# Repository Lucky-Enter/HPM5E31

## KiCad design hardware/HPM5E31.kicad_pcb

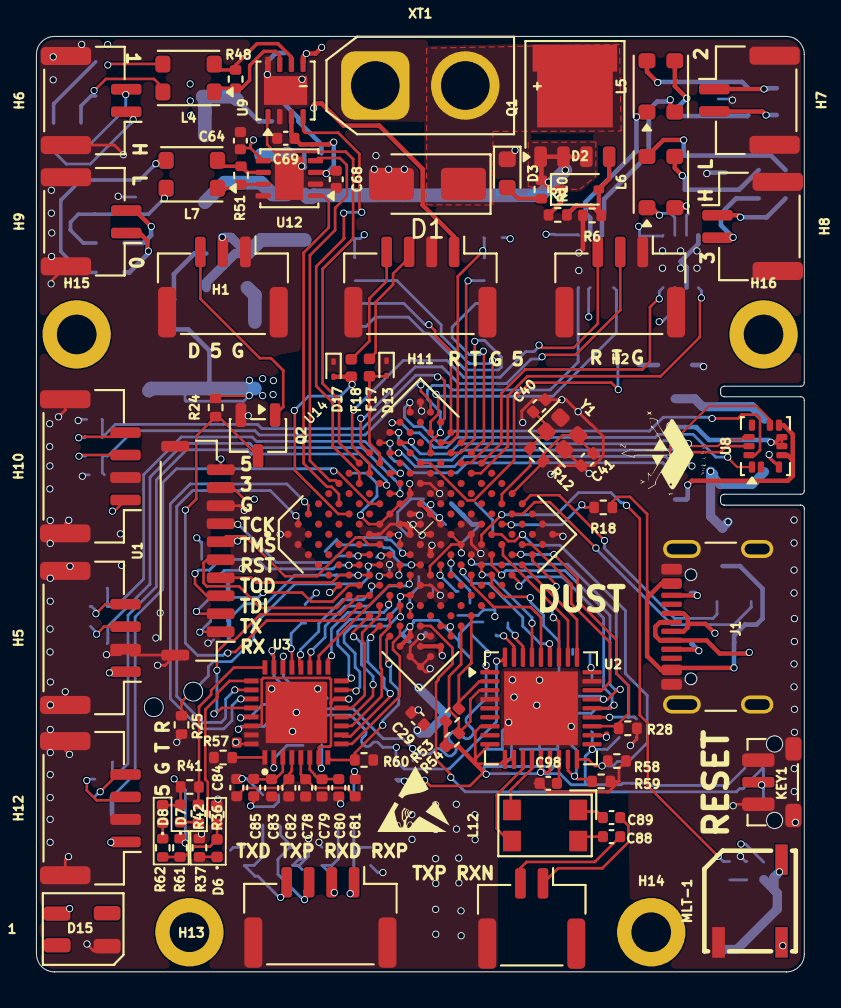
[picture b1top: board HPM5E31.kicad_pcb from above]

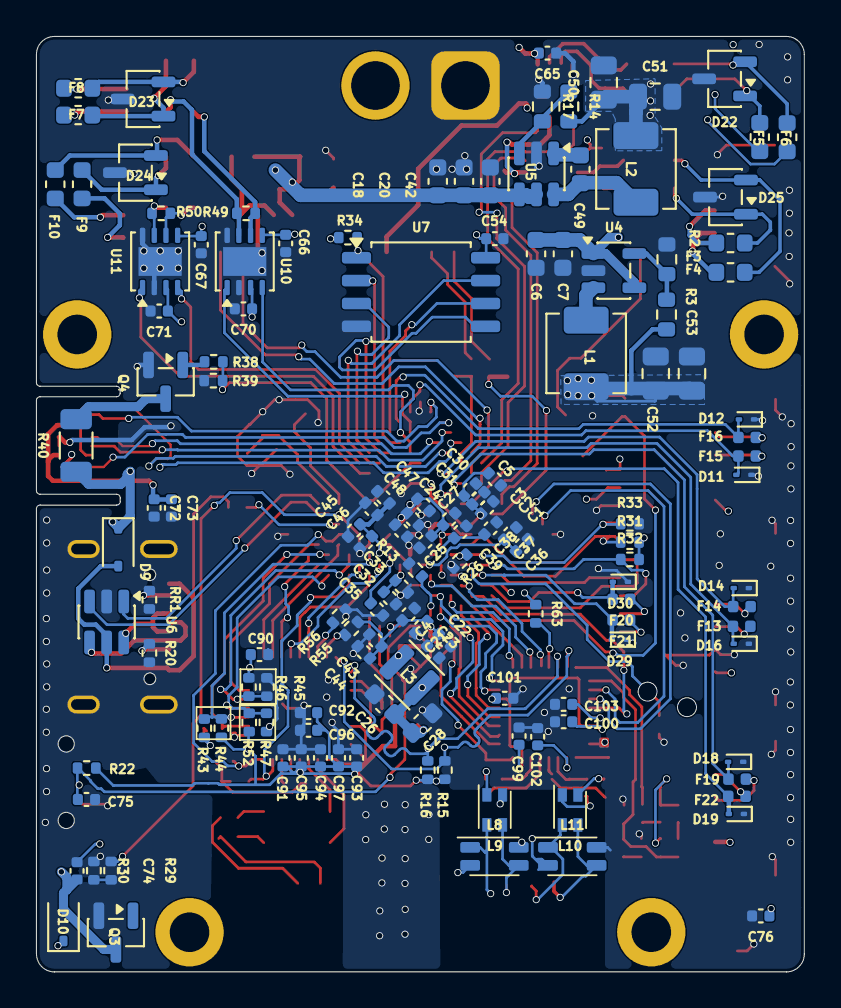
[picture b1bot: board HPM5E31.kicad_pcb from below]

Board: 4 copper layers, 42.7 x 52.0 mm, 223 parts (138 on the bottom side), 174 nets.

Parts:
C1, C2, C3, C4, C5, C22, C23, C24, C25, C27, C29, C30, C31, C32, C36, C38, C43, C46, C48, C54, C64, C65, C66, C67, C68, C69, C70, C71, C72, C73, C74, C75, C76, C80, C81, C84, C85, C88, C89, C90, C91, C92, C93, C94, C95, C96, C97, C99, C100, C101, C102, C103: 100nF; C_0402_1005Metric
C6, C7, C18, C20, C42: 10uF; C_0603_1608Metric
C21, C37, C39: 10uF; C_0402_1005Metric
C26, C28: 22uF; C_0603_1608Metric
C33, C35, C44, C45, C47: 4.7uF; C_0402_1005Metric
C40, C41: 12pF; C_0402_1005Metric
C49: 100nF; C_0603_1608Metric
C50, C51, C52, C53: 22uF 10V; C_0805_2012Metric
C78, C79, C82, C83: 10pF; C_0402_1005Metric
C98: 470nF; C_0402_1005Metric
D1: SMBJ30A; D_SMA
D2: BZT52C12S WH; D_SOD-323
D3: Blue; LED_0603_1608Metric
D6, D8: LED_G; LED_0402_1005Metric
D7: LED_E; LED_0402_1005Metric
D9: SD103AWS; D_SOD-323
D10: SD103AWS S4; D_SOD-323
D11, D12, D13, D14, D16, D17, D18, D19, D29, D30: ESD9B5.0ST5G; D_SOD-923
D15: WS2812B; LED_WS2812B-Mini_PLCC4_3.5x3.5mm
D22, D23, D24, D25: PESD1CAN; SOT-23-3
F3, F4, F5, F6, F7, F8, F9, F10: BSMD0603-005-15V; Fuse_0603_1608Metric
F13, F14, F15, F16, F17, F18, F19, F20, F21, F22: SMD0402; Fuse_0402_1005Metric
H1, H2: JST_GH_BM03B-GHS-TBT_1x03-1MP_P1.25mm_Vertical
H3: PH2.0; JST_GH_BM04B-GHS-TBT_1x04-1MP_P1.25mm_Vertical
H4: PH2.0; JST_GH_BM02B-GHS-TBT_1x02-1MP_P1.25mm_Vertical
H5, H10, H11, H12: JST_GH_BM04B-GHS-TBT_1x04-1MP_P1.25mm_Vertical
H6, H7, H8, H9: JST_GH_BM02B-GHS-TBT_1x02-1MP_P1.25mm_Vertical
H13, H14, H15, H16: MountingHole_Pad_MP; MountingHole_2.2mm_M2_DIN965_Pad
J1: USB_C_Receptacle_USB2.0_16P; USB_C_Receptacle_GCT_USB4105-xx-A_16P_TopMnt_Horizontal
KEY1: 笑脸开关3*5; SW_Push_1P1T-MP_NO_Horizontal_Alps_SKRTLAE010
L1, L2: 4.7uH; L_APV_APH0420
L3: 4.7uH; L_Wuerth_PMCI-252010
L4, L5, L6, L7: ACM2012(90欧); L_CommonModeChoke_Coilank_ACM3225
L8, L11: 3416自耦环; L_CommonMode_Wurth_WE-CNSW-1206
L9, L10: 2012共模环; L_CommonModeChoke_Coilcraft_0805USB
L12: 2012共模环; L_CommonModeChoke_Coilcraft_1812CAN
MLT-1: BUZ-SMD_L5.0-W5.5-P4.60
Q1: AGM60P100A; PQFN-8-EP_6x5mm_P1.27mm_Generic
Q2: PMBT3904; SOT-23-3
Q3: PMBT3904; SOT-23
Q4: AO3404A; SOT-23
R2: 10K; R_0603_1608Metric
R3: 45K; R_0603_1608Metric
R6, R9, R10, R13, R22, R25, R26, R28, R30, R31, R32, R33, R34, R39, R43, R44, R45, R46, R47, R52, R53, R54, R55, R56, R58, R59, R60, R63: 10K; R_0402_1005Metric
R12: 1M; R_0402_1005Metric
R14: 270K; R_0603_1608Metric
R15, R16, R20, R24, R36, R41, R61: 4.7K; R_0402_1005Metric
R17: 51K; R_0603_1608Metric
R18: 10R; R_0402_1005Metric
R29: 1K; R_0402_1005Metric
R37, R42, R62: 330R; R_0402_1005Metric
R38: 33R; R_0402_1005Metric
R40: 36R; R_1206_3216Metric
R48, R49, R50, R51: 120; R_0402_1005Metric
R57: 2.49K; R_0402_1005Metric
RR1: 4.7K; R_0402_1005Metric
U1: JST_SH_BM10B-SRSS-TB_1x10-1MP_P1.00mm_Vertical
U2: TJA1101B; QFN-36-1EP_6x6mm_P0.5mm_EP4.1x4.1mm
U3: RTL8201F-VB-CG
U4: RY3430; SOT-23-5
U5: RY8411; SOT-23-6
U6: USBLC6-2SC6; SOT-23-6
U7: W25Q128JVS; SOIC-8_5.3x5.3mm_P1.27mm
U8: ICM-42688P-HXY; LGA-14_3x2.5mm_P0.5mm_LayoutBorder3x4y
U9, U10, U11, U12: TJA1042TK-3; HVSON-8-1EP_3x3mm_P0.65mm_EP1.6x2.4mm
U14: HPM5E31IGN1; BGA-196_14x14_12.0x12.0mm_P0.8mm
XT1: AMASS_XT30U-M_1x02_P5.0mm_Vertical
Y1: 24M; Crystal_SMD_2016-4Pin_2.0x1.6mm

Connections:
3.3V: C1.2, C2.2, C3.2, C4.2, C5.2, C21.1, C22.1, C23.1, C43.2, C44.2, C45.2, C46.2, C47.2, C48.2, C52.1, C53.1, C54.1, C64.2, C65.2, C66.2, C67.2, C72.1, C73.1, C90.1, C91.1, C92.1, C93.2, C94.2, C95.2, C96.2, C97.2, C99.1, C100.1, C101.1, D7.2 (A), D8.2 (A), L1.2, R3.1, R15.2, R16.2, R22.2, R24.2, R31.2, R32.2, R34.2, R41.1, R44.1, R46.1, R52.1, R53.1, R54.1, R55.1, R61.1, R63.1, U1.9, U2.7 (VDDA(3V3)), U2.9 (V_BAT), U2.10 (INH), U2.11 (VDDA(TX)), U2.14 (VDDA(TX)), U2.15 (VDDD(3V3)), U2.19 (~VDD(IO)), U2.27 (~VDD(IO)), U3.7 (AVDD33), U3.14 (DVDD33), U3.30 (AVDD33), U7.8 (VCC), U8.5 (VDDIO), U8.8 (VDD), U9.5 (VIO), U10.5 (VIO), U11.5 (VIO), U12.5 (VIO), U14.E6 (VIO_B01), U14.E7 (VIO_B01), U14.E8 (VIO_B01), U14.E9 (VIO_B01), U14.J9 (VANA), U14.K6 (VIO_B01), U14.K9 (VREFH), U14.M1 (DCDC_IN), U14.M2 (DCDC_IN), U14.N4 (VPMC), U14.P4 (VPMC)
+1V2: C24.1, C25.1, C26.1, C27.1, C28.1, C29.1, C30.1, C31.1, L3.1, U14.F6 (VDD_SOC), U14.F9 (VDD_SOC), U14.G6 (VDD_SOC), U14.G9 (VDD_SOC), U14.H9 (VDD_SOC)
+5V: C6.1, C7.1, C50.1, C51.1, C68.1, C69.1, C70.1, C71.1, C74.1, C76.1, D9.1 (K), D10.1 (K), D15.1 (VDD), H1.2, H5.1, H10.1, H11.1, H12.1, L2.2, MLT-1.1 (+), R14.2, R40.1, U1.10, U4.1 (EN), U4.4 (IN), U9.3 (VCC), U10.3 (VCC), U11.3 (VCC), U12.3 (VCC)
BOOT0: R25.2, U14.G4 (PA02/GPTMR1.COMP1/UART0.DE/UART0.RTS/I2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)
BOOT1: R26.2, U14.G5 (PA03/GPTMR1.CAPT1/UART0.CTS/I2C2.SDA/MC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)
CAN0_H: F3.2, H9.2
CAN0_L: F4.2, H9.1
CAN0_RXD: U12.4 (RXD), U14.A6 (PC01/GPTMR1.CAPT0/UART0.RXD/MCAN0.RXD/E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)
CAN0_TXD: U12.1 (TXD), U14.B5 (PC00/GPTMR1.COMP0/UART0.TXD/MCAN0.TXD/E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)
CAN1_H: F5.2, H6.2
CAN1_L: F6.2, H6.1
CAN1_RXD: U9.4 (RXD), U14.B7 (PC04/UART1.CTS/SPI0.SCLK/MCAN1.RXD/ESC0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)
CAN1_TXD: U9.1 (TXD), U14.A8 (PC05/GPTMR1.COMP2/UART1.DE/UART1.RTS/SP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)
CAN2_H: F7.2, H7.2
CAN2_L: F8.2, H7.1
CAN2_RXD: U10.4 (RXD), U14.D12 (PD09/I2C0.SDA/MCAN2.RXD/ESC0.GPI22/ESC0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)
CAN2_TXD: U10.1 (TXD), U14.C13 (PD08/I2C0.SCL/MCAN2.TXD/ESC0.GPI23/ESC0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)
CAN3_H: F9.2, H8.2
CAN3_L: F10.2, H8.1
CAN3_RXD: U11.4 (RXD), U14.G14 (PD14/MCAN3.RXD/ESC0.GPI17/ESC0.GPO46/PP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)
CAN3_TXD: U11.1 (TXD), U14.G13 (PD15/MCAN3.TXD/ESC0.GPI16/ESC0.GPO47/PP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)
COL: U3.27 (COL), U14.A3 (PB26/ESC0.CTR6/XPI0.CA_D2/QEI1.H1/SDM0.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)
CRS: U3.26 (CRS/CRS_DV), U14.A2 (PB24/ESC0.CTR4/XPI0.CA_CS1/SDM0.CLK3/ET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)
DBUS: H1.3, Q2.1 (B)
ENET_PHY_LED0: R41.2, R42.2, U3.24 (LED0/PHYAD0/PMEB)
ENET_PHY_LED1: D6.2 (A), R36.1, R61.2, R62.2, U3.25 (LED1/PHYAD1)
ESC0_MDC: R16.1, U2.1 (MDC), U3.22 (MDC), U14.H5 (PA31/GPTMR2.COMP3/UART7.TXD/SPI3.DAT3/E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)
ESC0_MDIO: R15.1, U2.36 (MDIO), U3.23 (MDIO), U14.H4 (PA30/UART7.RXD/SPI3.DAT2/ESC0.MDIO/ETH0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)
ESC0_P0_RXCK: U3.13 (RXC), U14.J2 (PA21/GPTMR3.COMP2/UART5.DE/UART5.RTS/SP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)
ESC0_P0_RXD0: U3.9 (RXD0), U14.L2 (PA17/GPTMR3.CAPT0/UART4.RXD/ESC0.P0_RXD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)
ESC0_P0_RXD1: U3.10 (RXD1), U14.K1 (PA18/GPTMR3.COMP1/UART4.DE/UART4.RTS/ES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)
ESC0_P0_RXD2: U3.11 (RXD2/INTB), U14.K2 (PA19/GPTMR3.CAPT1/UART4.CTS/SPI3.CS3/ES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)
ESC0_P0_RXD3: U3.12 (RXD3/CLK_CTL), U14.J1 (PA20/UART5.CTS/SPI2.SCLK/ESC0.P0_RXD3/S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)
ESC0_P0_RXDV: R60.2, U3.8 (RXDV), U14.L1 (PA16/GPTMR3.COMP0/UART4.TXD/ESC0.P0_RXD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)
ESC0_P0_RXER: U3.28 (RXER/FXEN), U14.H2 (PA23/GPTMR2.COMP0/UART5.TXD/SPI2.MOSI/E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)
ESC0_P0_TXCK: U3.15 (TXC), U14.K3 (PA24/GPTMR2.COMP1/UART6.TXD/SPI3.CS2/ES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)
ESC0_P0_TXD0: U3.16 (TXD0), U14.K4 (PA25/GPTMR2.CAPT1/UART6.RXD/SPI3.CS1/ES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)
ESC0_P0_TXD1: U3.17 (TXD1), U14.J3 (PA26/GPTMR2.COMP2/UART6.DE/UART6.RTS/SP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)
ESC0_P0_TXD2: U3.18 (TXD2), U14.J4 (PA27/UART6.CTS/SPI3.CS0/ESC0.P0_TXD2/QE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)
ESC0_P0_TXD3: U3.19 (TXD3), U14.J5 (PA28/UART7.CTS/SPI3.MISO/ESC0.P0_TXD3/E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)
ESC0_P0_TXEN: U3.20 (TXEN), U14.H3 (PA29/GPTMR3.COMP3/UART7.DE/UART7.RTS/SP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)
ESC0_P1_RXCK: U2.25 (RXC/REF_CLK), U14.N12 (PF13/I2C1.SCL/MCAN3.STBY/ESC0.P1_RXCK/P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)
ESC0_P1_RXD0: R45.2, R46.2, U2.24 (RXD0/PHYAD1), U14.M10 (PF09/I2C0.SDA/MCAN2.RXD/ESC0.P1_RXD0/PW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)
ESC0_P1_RXD1: R47.2, R52.2, U2.23 (RXD1/PHYAD2), U14.P10 (PF10/MCAN2.STBY/ESC0.P1_RXD1/PWM1.P2/TR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)
ESC0_P1_RXD2: R43.2, R44.2, U2.22 (RXD2/CONFIG0), U14.L9 (PF11/ESC0.P1_RXD2/PWM1.P3/TRGM.P11/ETH0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)
ESC0_P1_RXD3: R28.1, U2.21 (RXD3/CONFIG1), U14.N11 (PF12/I2C1.SDA/ESC0.P1_RXD3/PWM1.P4/TRGM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)
ESC0_P1_RXDV: R58.2, U2.18 (RXDV/CONFIG2/CRSDV), U14.L11 (PF08/I2C0.SCL/MCAN2.TXD/ESC0.P1_RXDV/PW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)
ESC0_P1_RXER: R59.2, U2.17 (RXER/CONFIG3/TXCLK), U14.N9 (PF14/MCAN3.RXD/ESC0.P1_RXER/PWM1.P6/TRG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)
ESC0_P1_TXCK: U2.28 (TXC), U14.P11 (PF02/I2C2.SCL/MCAN0.STBY/ESC0.P1_TXCK/P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)
ESC0_P1_TXD0: U2.33 (TXD0), U14.M9 (PF03/I2C2.SDA/MCAN1.STBY/ESC0.P1_TXD0/P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)
ESC0_P1_TXD1: U2.32 (TXD1), U14.M8 (PF04/MCAN1.RXD/ESC0.P1_TXD1/PWM0.P4/TRG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)
ESC0_P1_TXD2: U2.31 (TXD2), U14.L8 (PF05/MCAN1.TXD/ESC0.P1_TXD2/PWM0.P5/TRG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)
ESC0_P1_TXD3: U2.30 (TXD3), U14.P12 (PF06/I2C3.SDA/ESC0.P1_TXD3/PWM0.P6/TRGM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)
ESC0_P1_TXEN: U2.29 (~TXEN), U14.M11 (PF07/I2C3.SCL/ESC0.P1_TXEN/PWM0.P7/TRGM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)
ESC0_REFCK: U2.20 (CLK_IN_OUT), U3.32 (CKXTAL2), U14.F1 (PA09/GPTMR0.CAPT1/UART2.RXD/I2C0.SDA/MC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)
ETH0_INT: R53.2, U2.2 (~INT_N), U14.P6 (PF26/SDM0.DAT1/ADC0.IN01/ADC1.IN01/ACMP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)
ETH0_RESET: R54.2, U2.3 (~RST_N), U14.P5 (PF28/SDM0.DAT3/ADC0.IN05/ADC1.IN05/ACMP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)
GND: C1.1, C2.1, C3.1, C4.1, C5.1, C6.2, C7.2, C18.2, C20.2, C21.2, C22.2, C23.2, C24.2, C25.2, C26.2, C27.2, C28.2, C29.2, C30.2, C31.2, C32.1, C33.1, C35.1, C36.1, C37.1, C38.1, C39.1, C40.2, C41.1, C42.2, C43.1, C44.1, C45.1, C46.1, C47.1, C48.1, C50.2, C51.2, C52.2, C53.2, C54.2, C64.1, C65.1, C66.1, C67.1, C68.2, C69.2, C70.2, C71.2, C72.2, C73.2, C75.2, C76.2, C78.2, C79.2, C82.2, C83.2, C90.2, C91.2, C92.2, C93.1, C94.1, C95.1, C96.1, C97.1, C98.1, C99.2, C100.2, C101.2, C102.2, C103.2, D1.2 (A2), D3.1 (K), D11.1 (A1), D12.1 (A1), D13.1 (A1), D14.1 (A1), D15.3 (VSS), D16.1 (A1), D17.1 (A1), D18.1 (A1), D19.1 (A1), D22.3 (A), D23.3 (A), D24.3 (A), D25.3 (A), D29.1 (A1), D30.1 (A1), H1.1, H1.MP, H2.1, H2.MP, H3.MP, H4.MP, H5.2, H5.MP, H6.MP, H7.MP, H8.MP, H9.MP, H10.2, H10.MP, H11.2, H11.MP, H12.2, H12.MP, J1.A1 (GND), J1.A12 (GND), J1.B1 (GND), J1.B12 (GND), J1.SH (SHIELD), KEY1.1, KEY1.MP, L8.2, L8.4, L11.2, L11.4, MLT-1.3 (NC), Q2.2 (E), Q3.2 (E), Q4.2 (S), R2.2, R6.2, R13.2, R17.1, R20.2, R25.1, R26.1, R28.2, R30.2, R33.2, R36.2, R37.2, R39.1, R43.1, R45.1, R47.1, R56.1, R57.1, R58.1, R59.1, R60.1, RR1.2, U1.8, U1.MP, U2.4 (SEL_1V8), U2.26 (GND), U2.37 (EP), U3.31 (CKXTAL1), U3.33 (EP), U4.2 (GND), U5.2 (GND), U6.2 (GND), U7.4 (GND), U8.6 (GNDIO), U8.7 (GND), U9.2 (GND), U9.8 (STB), U9.9 (GND), U10.2 (GND), U10.8 (STB), U10.9 (GND), U11.2 (GND), U11.8 (STB), U11.9 (GND), U12.2 (GND), U12.8 (STB), U12.9 (GND), U14.A1 (VSS), U14.A14 (VSS), U14.E5 (VSS), U14.E10 (VSS), U14.F7 (VSS), U14.F8 (VSS), U14.G7 (VSS), U14.G8 (VSS), U14.H7 (VSS), U14.H8 (VSSA), U14.J7 (VSS), U14.J8 (VREFL), U14.K5 (VSS), U14.K10 (VSS), U14.N1 (DCDC_GND), U14.N3 (VSS), U14.P1 (VSS), U14.P2 (DCDC_GND), U14.P14 (VSS), XT1.1 (-), Y1.2 (G), Y1.4 (G)
INT1: U8.4 (INT1), U14.A10 (PC18/GPTMR3.COMP1/UART4.DE/UART4.RTS/ES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)
INT2: U8.9 (INT2), U14.B10 (PC19/GPTMR3.CAPT1/UART4.CTS/SPI2.CS3/ES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)
JTAG_TCK: R33.1, U1.7, U14.F4 (PA06/GPTMR0.CAPT0/UART1.RXD/I2C3.SDA/SP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)
JTAG_TDI: R32.1, U1.3, U14.F3 (PA05/GPTMR1.COMP2/UART1.DE/UART1.RTS/SP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)
JTAG_TDO: U1.4, U14.F2 (PA04/UART1.CTS/SPI1.SCLK/MCAN1.RXD/PWM0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)
JTAG_TMS: R31.1, U1.6, U14.F5 (PA07/GPTMR0.COMP0/UART1.TXD/I2C3.SCL/SP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)
JTAG_TRST: U1.5, U14.G1 (PA08/GPTMR0.COMP1/UART2.TXD/I2C0.SCL/MC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)
MDI+0: C83.1, C85.1, U3.3 (MDI+0)
MDI+1: C78.1, C81.1, U3.5 (MDI+1)
MDI-0: C82.1, C84.1, U3.4 (MDI-0)
MDI-1: C79.1, C80.1, U3.6 (MDI-1)
unnamed: C80.2, L9.4
unnamed: C81.2, L9.1
unnamed: C84.2, L10.4
unnamed: C85.2, L10.1
unnamed: C88.1, L12.4
unnamed: C89.1, L12.3
unnamed: D2.2 (A), Q1.G, R6.1, R9.2
unnamed: D3.2 (A), R10.2
unnamed: D6.1 (K), R37.1
unnamed: D7.1 (K), R42.1
unnamed: D8.1 (K), R62.1
unnamed: C74.2, D10.2 (A), MLT-1.2 (-), Q3.3 (C)
unnamed: D22.1 (K), F5.1, L4.4
unnamed: D22.2 (K), F6.1, L4.3
unnamed: D23.1 (K), F7.1, L5.3
unnamed: D23.2 (K), F8.1, L5.4
unnamed: D24.1 (K), F9.1, L6.3
unnamed: D24.2 (K), F10.1, L6.4
unnamed: D25.1 (K), F3.1, L7.4
unnamed: D25.2 (K), F4.1, L7.3
unnamed: F13.2, H5.3
unnamed: F14.2, H5.4
unnamed: F15.2, H10.3
unnamed: F16.2, H10.4
unnamed: F17.2, H11.3
unnamed: F18.2, H11.4
unnamed: F19.2, H12.3
unnamed: F20.1, U1.2
unnamed: F21.1, U1.1
unnamed: F22.2, H12.4
unnamed: H3.1, L8.1, L9.2
unnamed: H3.2, L8.3, L9.3
unnamed: H3.3, L10.2, L11.1
unnamed: H3.4, L10.3, L11.3
unnamed: J1.A5 (CC1), R20.1
unnamed: J1.B5 (CC2), RR1.1
unnamed: J1.A6 (D+), J1.B6 (D+), U6.6 (I/O1)
unnamed: J1.A7 (D-), J1.B7 (D-), U6.4 (I/O2)
unnamed: L3.2, U14.N2 (DCDC_LP), U14.P3 (DCDC_LP)
unnamed: Q4.3 (D), R40.2
unnamed: Q4.1 (G), R38.1
unnamed: R29.1, R30.1
unnamed: R55.2, U2.35 (EN)
unnamed: R56.2, U2.34 (TXER)
unnamed: C98.2, U2.16 (VDDD(1V8))
unnamed: C102.1, U3.2 (AVDD10OUT)
unnamed: C103.1, U3.29 (DVDD10OUT)
unnamed: R57.2, U3.1 (RSET)
unnamed: R2.1, R3.2, U4.5 (FB)
unnamed: L1.1, U4.3 (SW)
unnamed: C49.2, U5.1 (BS)
unnamed: R14.1, R17.2, U5.3 (FB)
unnamed: C49.1, L2.1, U5.6 (LX)
unnamed: L4.1, R48.2, U9.7 (CANH)
unnamed: L4.2, R48.1, U9.6 (CANL)
unnamed: L5.2, R49.2, U10.7 (CANH)
unnamed: L5.1, R49.1, U10.6 (CANL)
unnamed: L6.2, R50.2, U11.7 (CANH)
unnamed: L6.1, R50.1, U11.6 (CANL)
unnamed: L7.1, R51.2, U12.7 (CANH)
unnamed: L7.2, R51.1, U12.6 (CANL)
unnamed: R18.2, U14.L12 (USB0_VBUS)
unnamed: R13.1, U14.L3 (WKUP)
unnamed: C41.2, R12.1, U14.K14 (XTALI), Y1.3
unnamed: C40.1, R12.2, U14.K13 (XTALO), Y1.1
unnamed: C35.2, U14.K8 (VDD_OTPCAP)
unnamed: C36.2, C37.2, U14.J6 (VDD_PHY0CAP)
unnamed: C38.2, C39.2, U14.H6 (VDD_PHY1CAP)
unnamed: C32.2, C33.2, U14.K7 (VDD_PMCCAP)
PHYRSTB: R63.2, U3.21 (PHYRSTB)
PWM0_P1: R29.2, U14.L10 (PF01/MCAN0.RXD/ESC0.MDIO/PWM0.P1/TRGM.P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)
PWM0_P4: R38.2, R39.2, U14.D11 (PD04/MCAN1.RXD/ESC0.GPI27/ESC0.GPO36/PP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)
RESET: C75.1, KEY1.2, R22.1, U14.M3 (RSTN)
RX_N: C89.2, H4.1
SPI2_CS: R34.1, U7.1 (~CS), U14.D13 (PC27/UART6.CTS/SPI2.CS0/ESC0.GPI36/ESC0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)
SPI2_D2: U7.3 (~WP/IO_{2}), U14.F14 (PC30/UART7.RXD/SPI2.DAT2/ESC0.GPI33/ESC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)
SPI2_D3: U7.7 (~HOLD/~RESET/IO_{3}), U14.F13 (PC31/GPTMR2.COMP3/UART7.TXD/SPI2.DAT3/E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)
SPI2_MISO: U7.2 (DO/IO_{1}), U14.E14 (PC28/UART7.CTS/SPI2.MISO/ESC0.GPI35/ESC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)
SPI2_MOSI: U7.5 (DI/IO_{0}), U14.E13 (PC29/GPTMR3.COMP3/UART7.DE/UART7.RTS/SP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)
SPI2_SCLK: U7.6 (CLK), U14.D14 (PC26/GPTMR2.COMP2/UART6.DE/UART6.RTS/SP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)
SPI3_CS: U8.12 (CSB), U14.B11 (PC21/GPTMR3.COMP2/UART5.DE/UART5.RTS/SP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)
SPI3_MISO: U8.1 (SDO/SA0), U14.A12 (PC22/GPTMR2.CAPT0/UART5.RXD/SPI3.MISO/E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)
SPI3_MOSI: U8.14 (SDX), U14.A13 (PC23/GPTMR2.COMP0/UART5.TXD/SPI3.MOSI/E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)
SPI3_SCLK: U8.13 (SCX), U14.A11 (PC20/UART5.CTS/SPI3.SCLK/ESC0.GPI43/ESC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)
TRX_N: L12.2, U2.13 (TRX_M)
TRX_P: L12.1, U2.12 (TRX_P)
TX_P: C88.2, H4.2
UART0_RX: D29.2 (A2), F21.2, U14.G3 (PA01/GPTMR1.CAPT0/UART0.RXD/MCAN0.RXD/P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)
UART0_TX: D30.2 (A2), F20.2, U14.G2 (PA00/GPTMR1.COMP0/UART0.TXD/MCAN0.TXD/P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)
UART1_RX: H2.3, U14.B8 (PC06/GPTMR0.CAPT0/UART1.RXD/I2C3.SDA/SP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)
UART1_TX: H2.2, U14.A9 (PC07/GPTMR0.COMP0/UART1.TXD/I2C3.SCL/SP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)
UART2_RX: D17.2 (A2), F18.1, U14.C5 (PC09/GPTMR0.CAPT1/UART2.RXD/I2C0.SDA/SP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)
UART2_TX: D13.2 (A2), F17.1, U14.B9 (PC08/GPTMR0.COMP1/UART2.TXD/I2C0.SCL/SP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)
UART3_RX: D19.2 (A2), F22.1, U14.D7 (PC14/UART3.RXD/SPI1.DAT2/MCAN3.RXD/ESC0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)
UART3_TX: D18.2 (A2), F19.1, U14.C8 (PC15/GPTMR0.COMP3/UART3.TXD/SPI1.DAT3/M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)
UART4_RX: D14.2 (A2), F14.1, U14.C9 (PC17/GPTMR3.CAPT0/UART4.RXD/ESC0.GPI46/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)
UART4_TX: D16.2 (A2), F13.1, U14.D8 (PC16/GPTMR3.COMP0/UART4.TXD/ESC0.GPI47/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)
UART5_RX: Q2.3 (C), R24.1, U14.H1 (PA22/GPTMR2.CAPT0/UART5.RXD/SPI2.MISO/E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)
UART6_RX: D12.2 (A2), F16.1, U14.C14 (PC25/GPTMR2.CAPT1/UART6.RXD/SPI2.CS1/ES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)
UART6_TX: D11.2 (A2), F15.1, U14.B14 (PC24/GPTMR2.COMP1/UART6.TXD/SPI2.CS2/ES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)
USB_DN: U6.3 (I/O2), U14.L13 (USB0_DN)
USB_DP: U6.1 (I/O1), U14.L14 (USB0_DP)
VBUS: D9.2 (A), J1.A4 (VBUS), J1.A9 (VBUS), J1.B4 (VBUS), J1.B9 (VBUS), R18.1, U6.5 (VBUS)
VIN: C18.1, C20.1, C42.1, D2.1 (K), Q1.S, R9.1, R10.1, U5.4 (EN), U5.5 (IN)
VIN1: D1.1 (A1), Q1.D, XT1.2 (+)
